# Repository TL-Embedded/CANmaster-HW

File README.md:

# CANmaster-HW

This is the hardware for the CANMaster USB to CAN adaptor.

See [CANmaster-FW](https://github.com/TL-Embedded/CANmaster-FW) for programming instructions and behavior description.

Hardware is done via KiCad. The processor is a STM32F072.

# USB
The STM32's native USB is used.

# CAN
The can interface is provided by either a `MCP2551-I/SN` or a `MAX33011EASA+`.
The MAX330 has better input protection, and reports error codes. The presense of the MAX330 shall be indicated by fitting 0R on R8.

The bus terminator is enabled in software via optoisolator.

The CAN bus is exposed via phoenix connector:

| Pin | Function |
| --- | -------- |
| 1   | CANL     |
| 2   | CANH     |
| 3   | GND      |

# Programming
Programming is done via a 6 pin TC2030 SWD interface.

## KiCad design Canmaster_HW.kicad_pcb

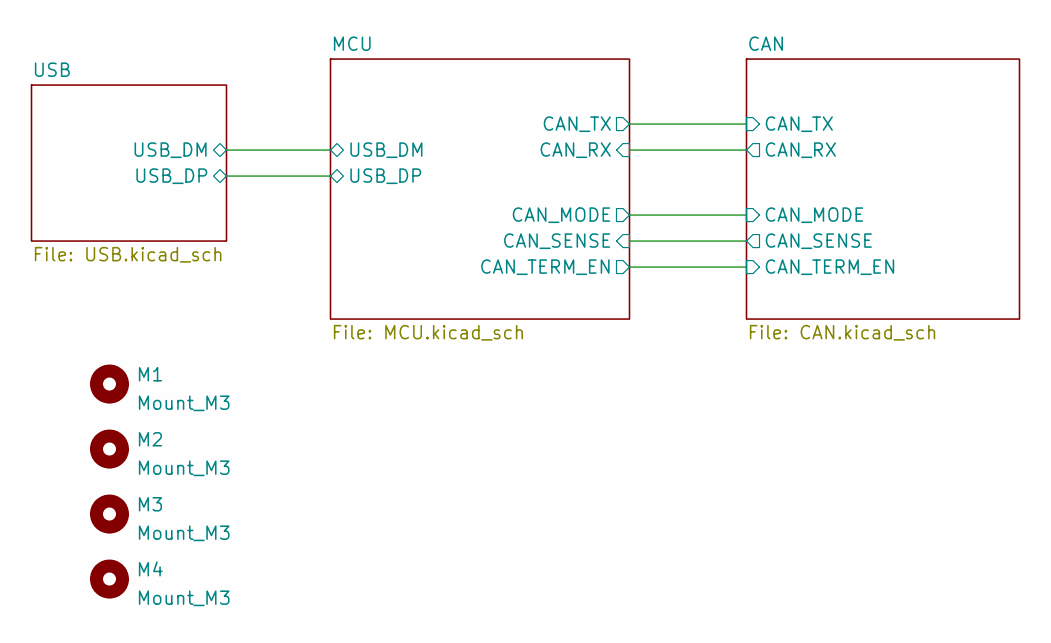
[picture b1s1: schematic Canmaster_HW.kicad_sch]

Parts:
M1, M2, M3, M4: Mount_M3

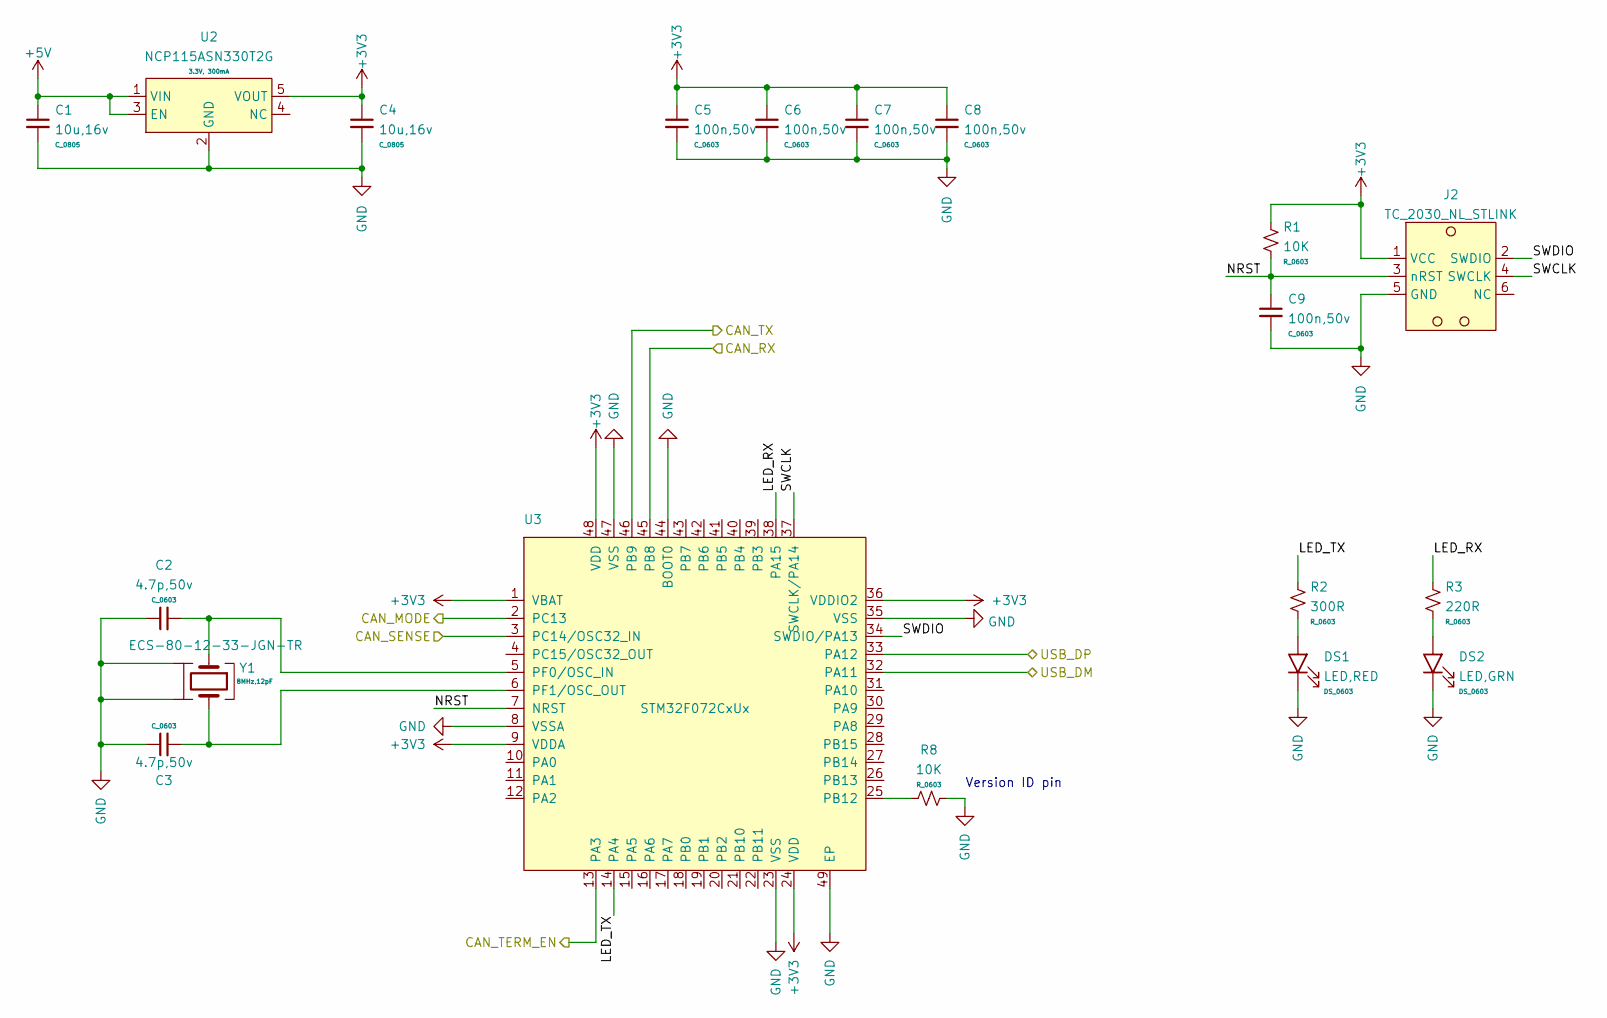
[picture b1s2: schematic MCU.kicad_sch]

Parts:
C1, C4: 10u,16v; C_0805
C2, C3: 4.7p,50v; C_0603
C5, C6, C7, C8, C9: 100n,50v; C_0603
DS1: LED,RED; DS_0603
DS2: LED,GRN; DS_0603
J2: TC_2030_NL_STLINK; TagConnect_2030_NL
R1, R8: 10K; R_0603
R2: 300R; R_0603
R3: 220R; R_0603
U2: NCP115ASN330T2G; SOT23_5
U3: STM32F072CxUx; QFN48_05_7x7_EP
Y1: ECS-80-12-33-JGN-TR; Crystal_SMD4_3.2x2.5

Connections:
+3V3: C4.1, C5.1, C6.1, C7.1, C8.1, J2.1 (VCC), R1.1, U2.5 (VOUT), U3.1 (VBAT), U3.9 (VDDA), U3.24 (VDD), U3.36 (VDDIO2), U3.48 (VDD)
+5V: C1.1, U2.1 (VIN), U2.3 (EN); also elsewhere on the board
/CAN/CAN_MODE: U3.2 (PC13); also elsewhere on the board
/CAN/CAN_RX: U3.45 (PB8); also elsewhere on the board
/CAN/CAN_SENSE: U3.3 (PC14/OSC32_IN); also elsewhere on the board
/CAN/CAN_TERM_EN: U3.13 (PA3); also elsewhere on the board
/CAN/CAN_TX: U3.46 (PB9); also elsewhere on the board
/MCU/LED_RX: R3.1, U3.38 (PA15)
/MCU/LED_TX: R2.1, U3.14 (PA4)
/MCU/NRST: C9.1, J2.3 (nRST), R1.2, U3.7 (NRST)
/MCU/SWCLK: J2.4 (SWCLK), U3.37 (SWCLK/PA14)
/MCU/SWDIO: J2.2 (SWDIO), U3.34 (SWDIO/PA13)
/MCU/USB_DM: U3.32 (PA11); also elsewhere on the board
/MCU/USB_DP: U3.33 (PA12); also elsewhere on the board
GND: C1.2, C2.1, C3.1, C4.2, C5.2, C6.2, C7.2, C8.2, C9.2, DS1.1 (K), DS2.1 (K), J2.5 (GND), R8.1, U2.2 (GND), U3.8 (VSSA), U3.23 (VSS), U3.35 (VSS), U3.44 (BOOT0), U3.47 (VSS), U3.49 (EP), Y1.2, Y1.4; also elsewhere on the board
unnamed: C2.2, U3.5 (PF0/OSC_IN), Y1.1
unnamed: C3.2, U3.6 (PF1/OSC_OUT), Y1.3
unnamed: DS1.2 (A), R2.2
unnamed: DS2.2 (A), R3.2
unnamed: R8.2, U3.25 (PB12)

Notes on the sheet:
Version ID pin

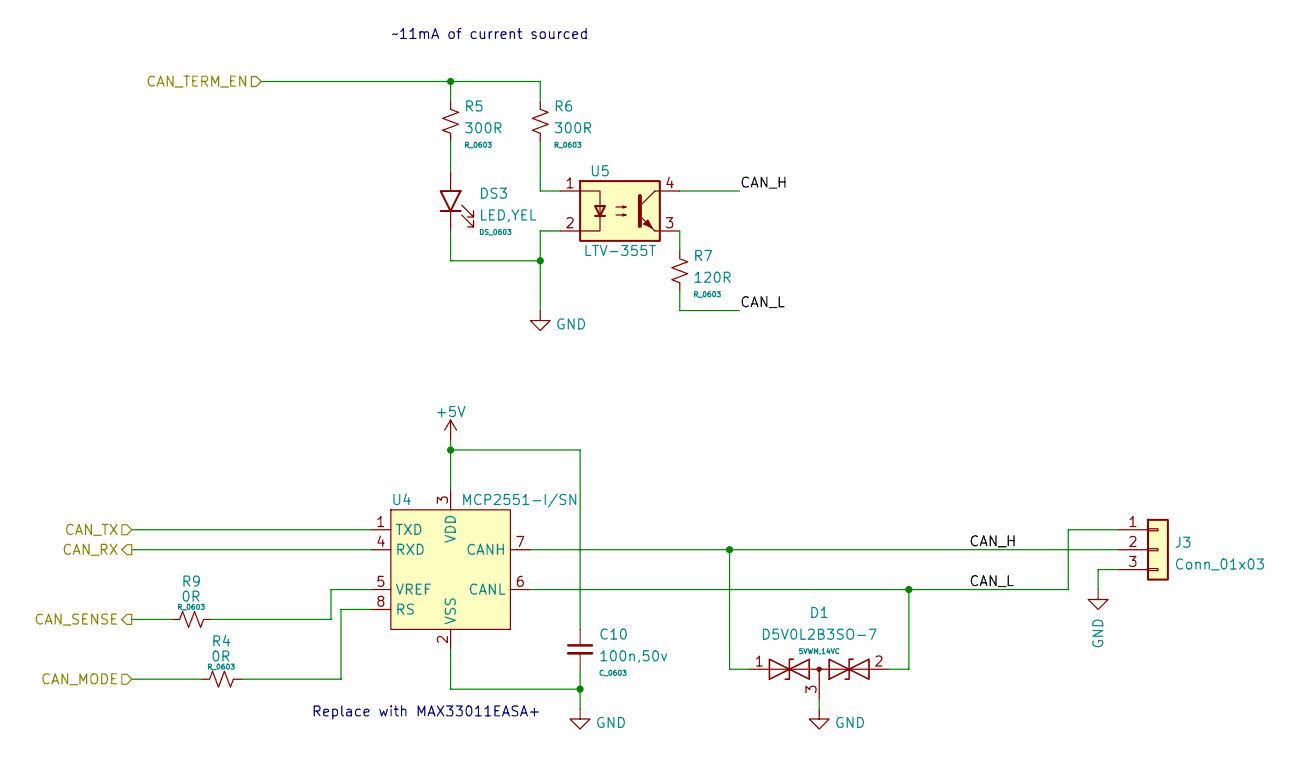
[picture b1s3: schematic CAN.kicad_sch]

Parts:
C10: 100n,50v; C_0603
D1: D5V0L2B3SO-7; SOT23_3
DS3: LED,YEL; DS_0603
J3: Conn_01x03; PhoenixContact_MSTBA_2,5_3-G-5,08_1x03_P5.08mm_Horizontal
R4, R9: 0R; R_0603
R5, R6: 300R; R_0603
R7: 120R; R_0603
U4: MCP2551-I/SN; SOIC_8
U5: LTV-355T; SO4_2.54_4.4x3.6

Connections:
+5V: C10.1, U4.3 (VDD); also elsewhere on the board
/CAN/CAN_H: D1.1 (A1), J3.2, U4.7 (CANH), U5.4
/CAN/CAN_L: D1.2 (A2), J3.1, R7.2, U4.6 (CANL)
/CAN/CAN_MODE: R4.1; also elsewhere on the board
/CAN/CAN_RX: U4.4 (RXD); also elsewhere on the board
/CAN/CAN_SENSE: R9.1; also elsewhere on the board
/CAN/CAN_TERM_EN: R5.1, R6.1; also elsewhere on the board
/CAN/CAN_TX: U4.1 (TXD); also elsewhere on the board
GND: C10.2, D1.3 (common), DS3.1 (K), J3.3, U4.2 (VSS), U5.2; also elsewhere on the board
unnamed: DS3.2 (A), R5.2
unnamed: R4.2, U4.8 (RS)
unnamed: R6.2, U5.1
unnamed: R7.1, U5.3
unnamed: R9.2, U4.5 (VREF)

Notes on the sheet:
~11mA of current sourced
Replace with MAX33011EASA+

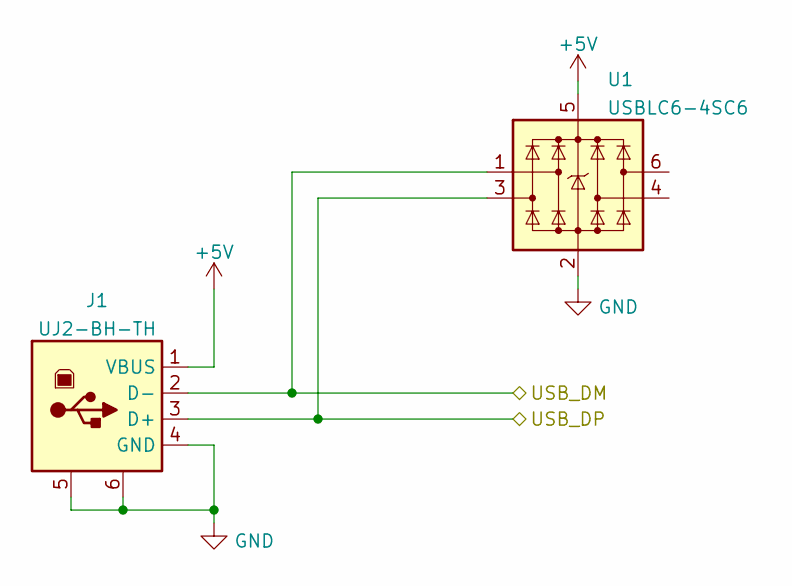
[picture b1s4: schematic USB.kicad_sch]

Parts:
J1: UJ2-BH-TH; USB_B_TH_Horizontal
U1: USBLC6-4SC6; SOT23_6

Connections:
+5V: J1.1 (VBUS), U1.5; also elsewhere on the board
/MCU/USB_DM: J1.2 (D-), U1.1; also elsewhere on the board
/MCU/USB_DP: J1.3 (D+), U1.3; also elsewhere on the board
GND: J1.4 (GND), J1.5, J1.6, U1.2; also elsewhere on the board

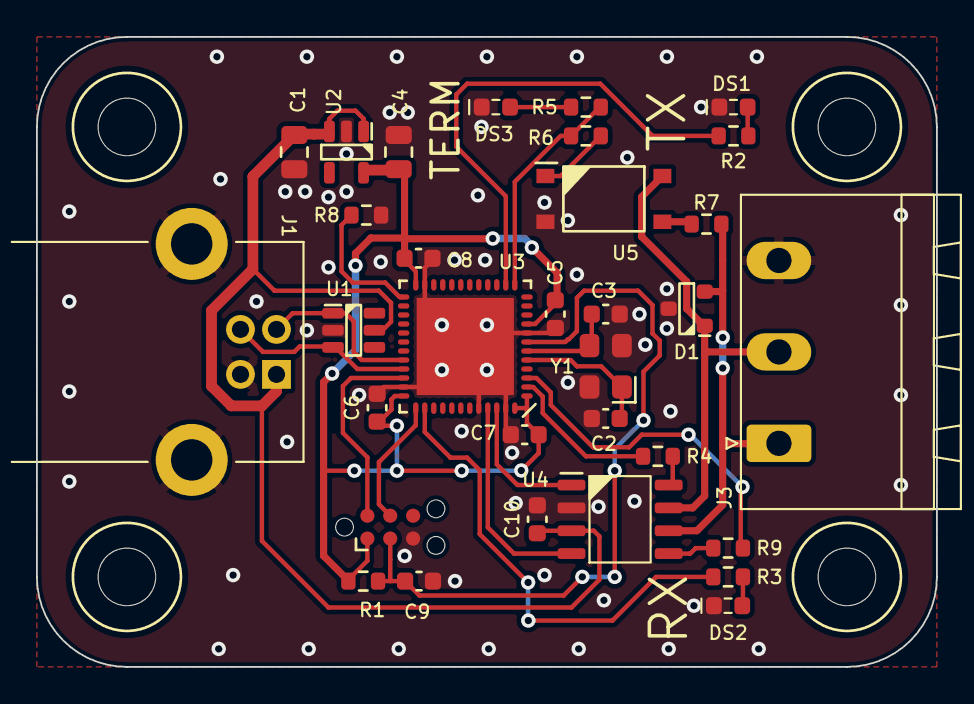
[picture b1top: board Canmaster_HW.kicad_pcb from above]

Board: 2 copper layers, 50.0 x 35.0 mm, 36 parts (0 on the bottom side), 27 nets.

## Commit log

2022-04-24 Initial import
2022-04-24 Moved TX & RX LED's
2022-04-24 Fix BOOT0 pin being disconnected
2022-05-29 Change RX LED to 220R
2022-06-11 Added connection for fault pin. Reversed CAN connector.
    Updated some footprints
2022-06-11 Correct LED colors
2022-06-11 Fix R3 & R9 label swap
2022-06-11 Rebuild pours
